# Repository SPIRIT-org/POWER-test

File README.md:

# POWER-test
PCB to test if the power system works

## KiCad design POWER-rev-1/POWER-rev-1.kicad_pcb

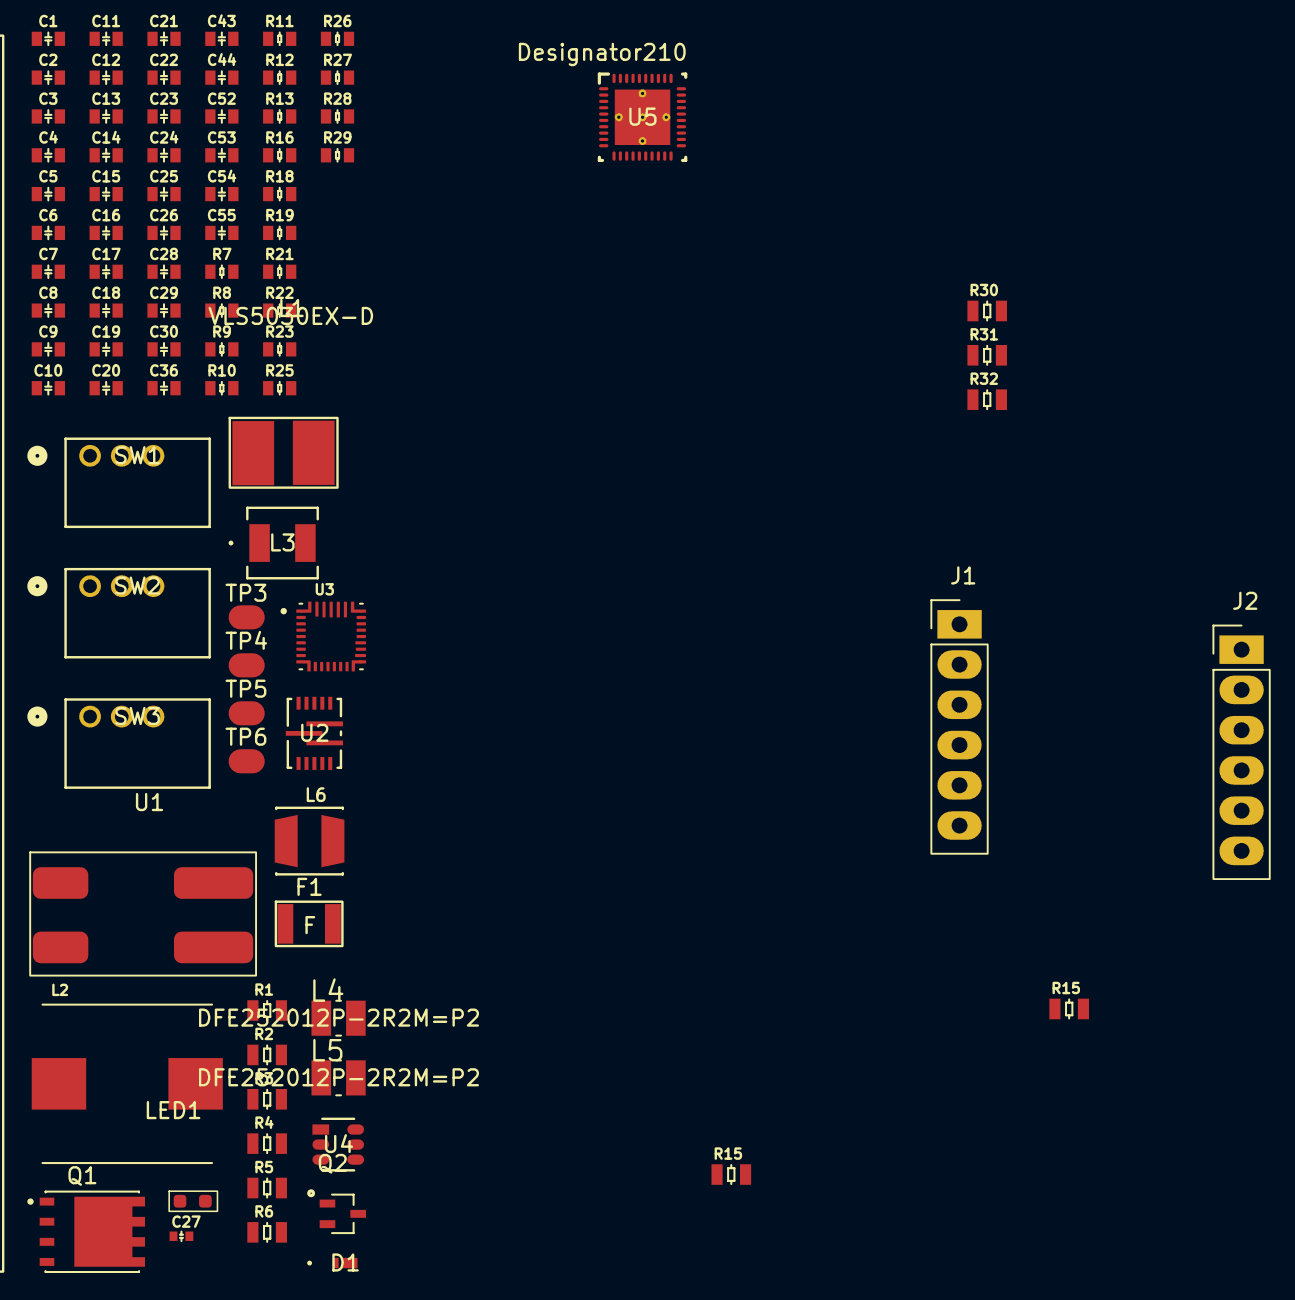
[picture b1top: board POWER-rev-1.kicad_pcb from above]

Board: 2 copper layers, 92 parts (0 on the bottom side), 57 nets, no tracks yet.

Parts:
BAT1: Li-ion-3.7 35Ah; battery_37V3500mAhLP685077JU
C1, C2, C3, C5, C11, C12, C14, C36, C43, C44: 22uF; 0603-capacitor
C4, C23, C52: 4.7uF; 0603-capacitor
C6, C8, C16, C18: 0.1uF; 0603-capacitor
C7: 6.8nF; 0603-capacitor
C9, C10: 47nF; 0603-capacitor
C13, C15, C17, C19, C20, C21, C22, C24, C25, C26, C30, C53, C54: 10uF; 0603-capacitor
C27: 1nF 50V; 0402-capacitor
C28, C29, C55: 1uF; 0603-capacitor
D1: D_Schottky; schottky-diode-CR_DSN2_152AB-C_OSI
F1: 9A 6V; PTC RESET FUSE 9.0A 6V 1210 1210L900SLPR
J1, J2: PINHD_1x6_Female; PinHeader_1x06_P2.54mm_Vertical
L1: 1.5uH; 1-5uH-inductor-VLS5030EX-D
L2: 2.2uH; 2-2uh-inductorIND_ETQP4M2R2KVC
L3: 6.8uH; 6-8uH-inductor-LQH44PN6R8MPRLIND_LQH44PN_PR_MUR
L4, L5: 2.2uH; 2-2uH-inductor-INDC2520X120N
L6: 3.3uH; 3-3uH-MURATA_LQH44PN3R3MPRL
LED1: 5mA 2V Fv; LED-INDICATOR-RED-QBLP601-R5
Q1: NMOS-BSC0902NSIATMA1-PG-TDSON-8-6-IC_ISC037N03L5ISATMA1
Q2: gpio-driver-transistor-fix-SOT65P210X110-3N
R1: 127kΩ; 0805-resistor
R2: 100kΩ; 0805-resistor
R3: 5.23kΩ; 0805-resistor
R4: 10kΩ; 0805-resistor
R5: 4.7KΩ; 0805-resistor
R6: 30kΩ; 0805-resistor
R7: 6.8kΩ; 0603-resistor
R8: 750kΩ; 0603-resistor
R9: 200kΩ; 0603-resistor
R10: 100Ω; 0603-resistor
R11, R12: 10kΩ; 0603-resistor
R13: 680Ω; 0603-resistor
R15, R15#2: 10Ω; 0805-resistor
R16: 680kΩ 1%; 0603-resistor
R18: 1MΩ 1%; 0603-resistor
R19, R21: 470kΩ 1%; 0603-resistor
R22: 820kΩ; 0603-resistor
R23: 182KΩ; 0603-resistor
R25, R26, R28, R29: 100kΩ; 0603-resistor
R27: 5Ω; 0603-resistor
R30, R31, R32: 0Ω; 0805-resistor
SW1: EG25-switch-CSS-1210MC; privacy-switch-SW3_CSS-1210MC_NDC
SW2: MIC-switch-CSS-1210MC; privacy-switch-SW3_CSS-1210MC_NDC
SW3: CAM-switch-CSS-1210MC; privacy-switch-SW3_CSS-1210MC_NDC
TP3, TP4, TP5, TP6: test-pad-1
U1: BAT-CONNECTOR-FLTS22WR00
U2: MP3429GL-Z; QFN-3x4_MP3429_MNP
U3: BQ25792RQMR; charger-bq25792-QFN40P400X400X100-29N
U4: 22V-boost-AP3032KTR-G1; SOT23-6_DIO
U5: TPS65023BRSBR

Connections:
1V8: J1.4, R31.2, SW2.1
3V3A: J1.2, R30.2
3V3B: J1.6, Q2.3 (S), R11.1, R12.2, R25.1, R28.1, R29.2, R32.2, SW3.1
5V: C8.1, C11.1, C12.1, C14.1, R8.1, U2.8 (VOUT)
22V: C55.1, D1.1 (K), U4.5 (OV)
AGND: C5.2, R7.2, R9.2, U2.6 (AGND), U2.9 (FTY), U5.17 (AGND2), U5.22 (LDO_EN), U5.32 (DEFDCDC2), U5.40 (AGND1), U5.41 (PAD)
BACKLIGHT-: R27.1, U4.3 (FB)
BAT+: C13.1, C15.1, F1.2, R10.2, U3.22 (BAT), U3.23 (BAT__1)
CAMSWITCH: Q2.2 (D), SW3.3
DEFDCDC1 DIVIDER: C36.1, J1.1, L6.1, R22.1, R30.1, U5.9 (VDCDC1)
EN3V3A SW OUT: SW1.3, U5.25 (DCDC1_EN)
GND: C1.2, C2.2, C3.2, C4.1, C8.2, C11.2, C12.2, C13.2, C14.2, C15.2, C16.2, C17.2, C18.2, C19.2, C20.2, C21.2, C22.2, C23.2, C24.2, C25.2, C26.2, C27.2, C28.2, C29.2, C30.2, C36.2, C43.2, C44.2, C52.1, C53.2, C54.2, C55.2, R2.2, R4.2, R5.1, R6.2, R19.1, R21.1, R23.1, R27.2, U1.4 (OUT-), U2.7 (PGND), U3.10 (ACDRV2), U3.11 (ACDRV1), U3.27 (GND), U4.2 (GND), U5.3 (PGND3), U5.8 (PGND1), U5.14 (VSYSIN), U5.15 (VBACKUP), U5.18 (VLDO2), U5.19 (VINLDO), U5.20 (VLDO1), U5.34 (PGND2)
unnamed: C7.2, R7.1
unnamed: D1.2 (A), L3.2, U4.1 (SW)
unnamed: LED1.2 (A), R13.1
unnamed: LED1.1 (K), R12.1, U3.1 (STAT)
unnamed: TP3.1 (A_1), U5.26 (TRESPWRON)
unnamed: TP4.1 (A_1), U5.11 (HOT_RESET_N)
unnamed: C52.2, TP5.1 (A_1), U5.16 (VRTC)
unnamed: F1.1, U1.3 (OUT+)
unnamed: C6.1, U2.13 (BST)
unnamed: C7.1, U2.4 (COMP)
unnamed: R8.2, R9.1, U2.5 (FB)
unnamed: C5.1, U2.3 (SS)
unnamed: C6.2, L1.2, U2.1 (SW)
unnamed: C4.2, U2.2 (VDD)
unnamed: R10.1, U3.18 (BATP)
unnamed: C9.2, U3.4 (BTST1)
unnamed: C10.2, U3.19 (BTST2)
unnamed: R1.1, R2.1, U3.17 (ILIM_HIZ)
unnamed: C16.1, C17.1, C19.1, C21.1, U3.29 (PMID)
unnamed: R5.2, U3.20 (PROG)
unnamed: C27.1, U3.24 (SDRV)
unnamed: C9.1, L2.2, U3.28 (SW1)
unnamed: C10.1, L2.1, U3.26 (SW2)
unnamed: R3.2, R4.1, R6.1, U3.16 (TS)
unnamed: R22.2, R23.2, U5.10 (DEFDCDC1)
unnamed: L6.2, U5.7 (L1)
unnamed: L4.2, U5.35 (L2)
unnamed: L5.2, U5.4 (L3)
unnamed: R18.1, R19.2, U5.39 (LOWBAT_SNS)
unnamed: R16.1, R21.2, U5.38 (PWRFAIL_SNS)
unnamed: C29.1, R15#2.2, R26.1, U5.37 (VCC)
unnamed: C43.1, J1.3, L4.1, R31.1, U5.33 (VDCDC2)
unnamed: C44.1, J1.5, L5.1, R32.1, U5.2 (VDCDC3)
unnamed: C30.1, J2.2, U5.6 (VINDCDC1)
unnamed: C53.1, J2.4, U5.36 (VINDCDC2)
unnamed: C54.1, J2.6, U5.5 (VINDCDC3)
REGN: C23.1, R1.2, R3.1, R13.2, U3.5 (REGN)
SCL PWR: U3.14 (SCL), U5.30 (SCLK)
SDA PWR: U3.15 (SDA), U5.29 (SDAT)
SYS: C1.1, C2.1, C3.1, C18.1, C20.1, C22.1, C24.1, C25.1, C26.1, C28.1, J2.1, J2.3, J2.5, L1.1, L3.1, R15#2.1, R16.2, R18.2, U2.10 (MODE), U2.11 (EN), U2.12 (VIN), U3.25 (SYS), U4.6 (VIN), U5.1 (DEFDCDC3)
USBC POW: U3.2 (VBUS), U3.8 (VAC2), U3.9 (VAC1)
~BQ INT: R11.2, U3.21 (~INT)
~LOW BAT: R26.2, U5.21 (LOW_BAT_N)
~PWRFAIL: R25.2, U5.31 (PWRFAIL_N)
~TPS INT: R28.2, TP6.1 (A_1), U5.28 (INT_N)
